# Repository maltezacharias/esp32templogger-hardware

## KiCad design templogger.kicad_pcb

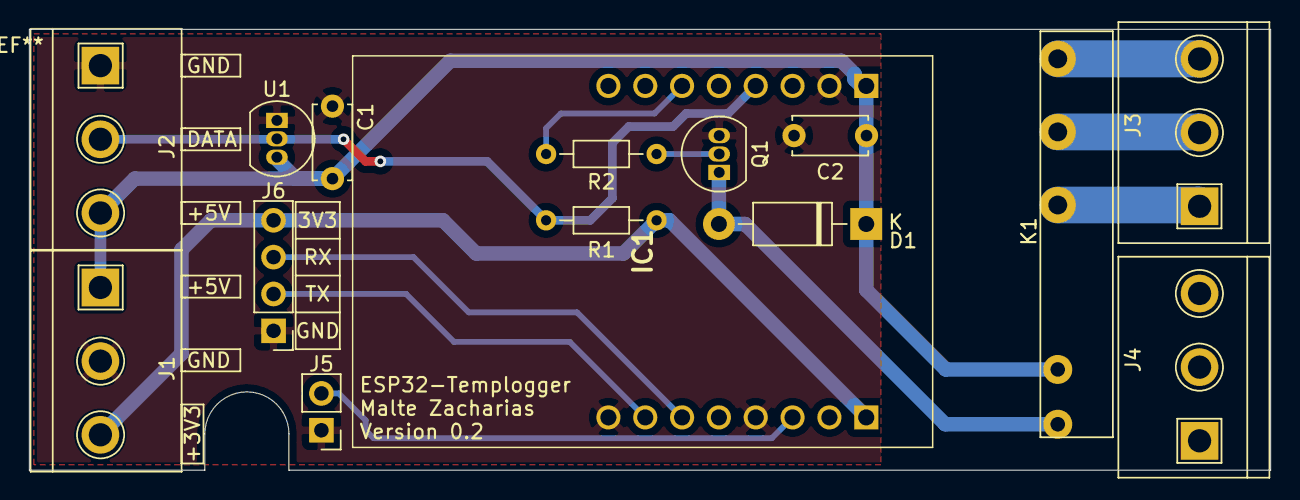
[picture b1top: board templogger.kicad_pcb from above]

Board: 2 copper layers, 85.6 x 30.4 mm, 15 parts (0 on the bottom side), 13 nets.

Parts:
C1, C2: 100nF; C_Disc_D5.0mm_W2.5mm_P5.00mm
D1: 1N4007; D_DO-41_SOD81_P10.16mm_Horizontal
IC1: ESP32-CAM; ESP32CAM-Header
J1, J2, J3, J4: DG129-5.08-03P-14; DG129-5.08-03P-12-00A
J5: Conn_01x02_Male; PinHeader_1x02_P2.54mm_Vertical
J6: Conn_01x04_Male; PinHeader_1x04_P2.54mm_Vertical
K1: HF41F_005-ZST; HF411-05-ZST
Q1: BC337; TO-92_Inline
R1: 4.7K; R_Axial_DIN0204_L3.6mm_D1.6mm_P7.62mm_Horizontal
R2: 10K; R_Axial_DIN0204_L3.6mm_D1.6mm_P7.62mm_Horizontal
U1: DS18B20; TO-92_Inline

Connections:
+3V3: IC1.9, J1.3, J6.4, R1.1
+5V: C1.1, C2.1, D1.1, IC1.8, J1.1, J2.3, K1.2, U1.3
/230V: J3.2, K1.4
/GPIO0: IC1.11, J5.2
/GPIO13: IC1.5, J2.2, R1.2, U1.2
/GPIO14: IC1.3, R2.2
/RX: IC1.14, J6.3
/TX: IC1.15, J6.2
GND: C1.2, C2.2, IC1.7, IC1.12, IC1.16, J1.2, J2.1, J5.1, J6.1, Q1.3, U1.1
unnamed: D1.2, K1.1, Q1.1
unnamed: J3.1, K1.3
unnamed: J3.3, K1.5
unnamed: Q1.2, R2.1

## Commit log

2020-12-28 Add Kicad ignores
2020-12-28 Add screw terminal shape
2020-12-28 Add Case 3D Shape
2020-12-28 Add Project Shape Library
2020-12-28 Add custom footprints
2020-12-28 v0.2
2020-12-28 Include sample render
2020-12-28 Add schematic sample
2020-12-28 Include schematic as image in README
